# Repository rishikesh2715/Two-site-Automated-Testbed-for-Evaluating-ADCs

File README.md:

# Two-site-Automated-Testbed-for-Evaluating-ADCs

## Overview
The Two-site Automated Test System (ATS-2) is a custom-designed testbed for evaluating ADCs, specifically focused on testing the ADS7816. This comprehensive testing solution consists of a custom-designed device interface board, National Instruments VirtualBench integration, and automated test programs implemented in Python.

### Key Features:
- **Dual Testing Sites**: Capability to test two ADC devices simultaneously
- **Comprehensive Test Suite**: Includes all relevant parametric and functional tests
- **Automated Control**: Python-based test automation for consistent results
- **Relay-Based Interface**: Flexible configuration using G5NB-1A4 DC24 and J104D2C24VDC.15S relays
- **Power Management**: External 24V power supply for relay control

## Test Capabilities
The ATS-2 supports a comprehensive suite of tests including:
- Continuity Testing
- Power Supply Current Testing (Normal and Power-down modes)
- Leakage Current Testing
- Input Impedance Testing
- Linear Histogram Method for Code Edge Measurements
- Sinusoidal Histogram Method for Code Edge Measurements
- Offset and Offset Error Analysis
- Gain and Gain Error Analysis
- Missing Code Detection
- Integral Nonlinearity (INL) Analysis
- Differential Nonlinearity (DNL) Analysis
- Maximum Sampling Frequency Verification

## Hardware Specifications
### Device Under Test (DUT)
- **Target Device**: ADS7816
- **Features**: 
  - 200kHz sampling rate
  - Low power operation
  - Differential input
  - Serial interface
  - External reference and clock requirements
  - 5V power source operation

### Relay System
- **SPST-NO Relay**: G5NB-1A4 DC24
  - Power consumption: ~200mW
  - Operating current: ~8.3mA at 24V
  - Cost: $1.32

- **DPDT Relay**: J104D2C24VDC.15S
  - Power consumption: 150mW
  - Operating current: ~6.25mA at 24V
  - Cost: $1.21

## Software
The testbed includes a comprehensive suite of Python scripts for automated testing:
- `Combined_Hist_Tests.py`: Manages both linear and sinusoidal histogram testing
- `Continuity.py`: Performs continuity testing across all pins
- `InputImpedanceTest.py`: Measures input impedance characteristics
- `LeakageCurrents.py`: Tests for current leakage under various conditions
- `PwrSupplyCurrents.py`: Evaluates power supply current in different operating modes
- `Testing_Comb.py`: Main test orchestration script

## Getting Started
1. **Hardware Setup**:
   - Connect the VirtualBench device (VB8012-30DF182)
   - Apply 24V external power for relay control
   - Connect the DUT to the test board

2. **Software Requirements**:
   - Python 3.x
   - PyVirtualBench library
   - Required Python packages: numpy, matplotlib, tqdm, pandas

3. **Running Tests**:
   ```bash
   python Testing_Comb.py

## PCBWay - PCB Manufacturing and Assembly

This project was proudly sponsored by **PCBWay**, a leading PCB manufacturer and assembler. They provided high-quality PCB manufacturing and assembly services, ensuring that the ATS-2 board was produced to the highest standards. Here's why PCBWay is a great choice for PCB production:

- **Exceptional Quality**: The PCBs produced by PCBWay have excellent build quality, with precise soldering and thorough assembly.
- **Fast Service**: PCBWay offers quick turnaround times, so your project can stay on track.
- **Comprehensive Services**: From prototyping to mass production, PCBWay provides services for all stages of PCB development, including multi-layer PCBs, advanced PCBs, flexible PCBs, and assembly services.
- **Affordable Pricing**: PCBWay offers competitive pricing without compromising quality.

To order this board through PCBWay:
1. Upload the provided Gerber files to PCBWay's portal
2. Select your preferences:
   - Min Track/spacing: 6/6 mil
   - Min hole size: 0.2mm
   - Recommended finish: Immersion Gold (ENIG)

If you're looking for a reliable partner to bring your PCB projects to life, check out [PCBWay](https://pcbway.com). With their extensive capabilities and top-notch customer support, PCBWay is the ideal choice for makers, engineers, and businesses alike.

## PCB Features
- Custom designed device interface board
- Relay-based switching matrix for flexible test configuration
- Support for dual device testing
- Professional 4-layer PCB design
- Integrated power management for both DUT and relay control
- Comprehensive test point access
- Industrial-grade components for reliability

## License
This project is open-source and available under the MIT License.

## Contributing
Contributions are welcome! Please feel free to submit pull requests or open issues for improvements and bug fixes.

## Acknowledgments
- Mr. Johnston and Dr. Dallas at Texas Tech University for project supervision
- National Instruments for VirtualBench support
- PCBWay for manufacturing partnership

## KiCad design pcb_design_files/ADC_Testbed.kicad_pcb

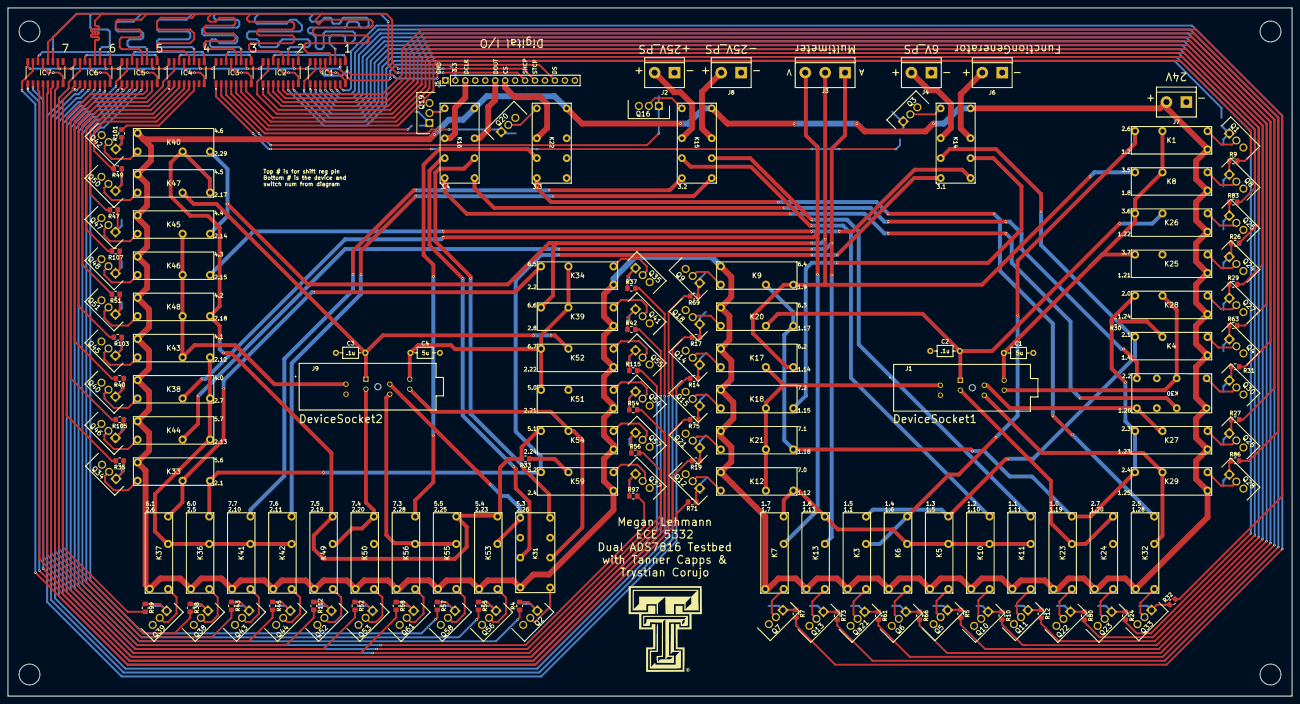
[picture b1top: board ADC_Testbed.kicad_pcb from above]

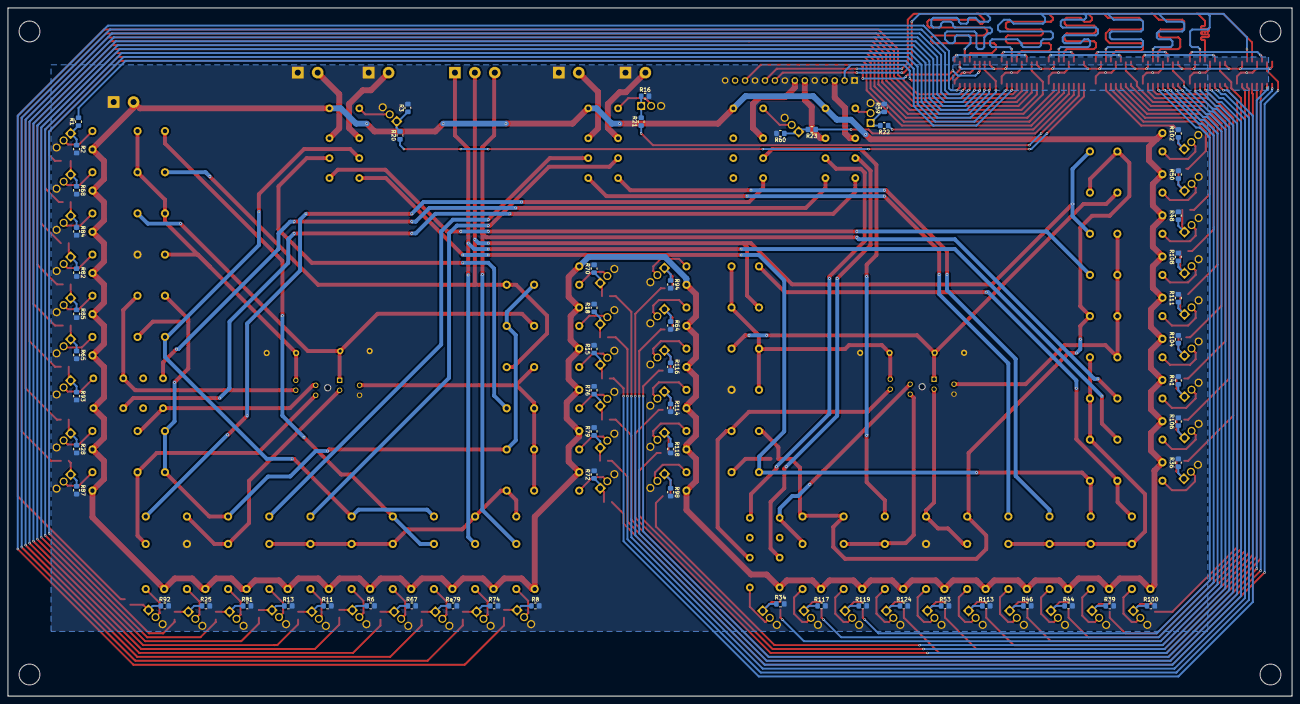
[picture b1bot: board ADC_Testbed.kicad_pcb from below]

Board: 2 copper layers, 327.5 x 175.5 mm, 238 parts (59 on the bottom side), 220 nets.

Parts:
C1, C4: 5u; C_Axial_L3.8mm_D2.6mm_P7.50mm_Horizontal
C2, C3: .1u; C_Axial_L3.8mm_D2.6mm_P7.50mm_Horizontal
IC1, IC2, IC3, IC4, IC5, IC6, IC7: 74LVC595AD_118; 74LVC595AD118
J1, J9: DNP; 3M_208-7391-55-1902
J2: +25V_PS; TerminalBlock_bornier-2_P5.08mm
J3: Multimeter; TerminalBlock_bornier-3_P5.08mm
J4: 6V_PS; TerminalBlock_bornier-2_P5.08mm
J5: Digital I/O; PinHeader_1x14_P2.54mm_Vertical
J6: FunctionGenerator; TerminalBlock_bornier-2_P5.08mm
J7: 24V; TerminalBlock_bornier-2_P5.08mm
J8: -25V_PS; TerminalBlock_bornier-2_P5.08mm
K1, K3, K4, K5, K6, K7, K8, K9, K10, K11, K12, K13, K17, K18, K20, K21, K23, K24, K25, K26, K27, K28, K29, K32, K33, K34, K36, K37, K38, K39, K40, K41, K42, K43, K44, K45, K46, K47, K48, K49, K50, K51, K52, K53, K54, K55, K56, K59: OJ-SS-112LMH2; G5NB1A4DC5
K14, K15, K16, K22, K30, K31: G6K-2P-Y_DC9; J104D2C24VDC.15S
Q1, Q2, Q3, Q4, Q5, Q6, Q7, Q8, Q9, Q10, Q11, Q12, Q13, Q14, Q15, Q16, Q18, Q19, Q20, Q21, Q22, Q23, Q24, Q25, Q26, Q27, Q28, Q30, Q33, Q34, Q35, Q37, Q38, Q39, Q40, Q41, Q42, Q43, Q44, Q45, Q46, Q47, Q48, Q50, Q51, Q52, Q53, Q54, Q55, Q56, Q57, Q58, Q61: IRL540PBF; TO254P465X1024X2050-3P
Qa21: IRL540PBF; TO254P465X1024X2050-3P
R1, R4, R5, R7, R9, R10, R12, R14, R17, R19, R20, R21, R22, R23, R24, R26, R27, R29, R31, R32, R35, R37, R38, R40, R42, R43, R45, R47, R49, R51, R52, R54, R55, R56, R57, R58, R61, R63, R66, R69, R71, R73, R75, R80, R83, R86, R97, R99, R101, R103, R105, R107, R112, R115: 2k; R_0805_2012Metric_Pad1.20x1.40mm_HandSolder
R2, R3, R6, R8, R11, R13, R15, R16, R18, R25, R28, R34, R36, R39, R41, R44, R46, R48, R50, R53, R59, R60, R64, R65, R67, R68, R70, R72, R74, R76, R79, R81, R82, R84, R85, R87, R92, R93, R94, R98, R100, R102, R104, R106, R108, R111, R113, R114, R116, R117, R118, R119, R124: 10k; R_0805_2012Metric_Pad1.20x1.40mm_HandSolder
R30, R33: 1R; R_0805_2012Metric_Pad1.20x1.40mm_HandSolder
Ra79: 10k; R_0805_2012Metric_Pad1.20x1.40mm_HandSolder

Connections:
0: J5.3, K16.6 (COM_2)
2: J5.6, K16.3 (COM_1)
3: J5.7, K22.6 (COM_2)
4: IC1.11 (SHCP), IC2.11 (SHCP), IC3.11 (SHCP), IC4.11 (SHCP), IC5.11 (SHCP), IC6.11 (SHCP), IC7.11 (SHCP), J5.9
5: IC1.12 (STCP), IC2.12 (STCP), IC3.12 (STCP), IC4.12 (STCP), IC5.12 (STCP), IC6.12 (STCP), IC7.12 (STCP), J5.10
6: IC1.14 (DS), J5.12
+3.3V: IC1.10 (~MR), IC1.16 (VCC), IC2.10 (~MR), IC2.16 (VCC), IC3.10 (~MR), IC3.16 (VCC), IC4.10 (~MR), IC4.16 (VCC), IC5.10 (~MR), IC5.16 (VCC), IC6.10 (~MR), IC6.16 (VCC), IC7.10 (~MR), IC7.16 (VCC), J5.2
+24V: J7.2, K1.2 (COIL_2), K3.2 (COIL_2), K4.2 (COIL_2), K5.2 (COIL_2), K6.2 (COIL_2), K7.2 (COIL_2), K8.2 (COIL_2), K9.2 (COIL_2), K10.2 (COIL_2), K11.2 (COIL_2), K12.2 (COIL_2), K13.2 (COIL_2), K14.1 (COIL_+), K15.1 (COIL_+), K16.1 (COIL_+), K17.2 (COIL_2), K18.2 (COIL_2), K20.2 (COIL_2), K21.2 (COIL_2), K22.1 (COIL_+), K23.2 (COIL_2), K24.2 (COIL_2), K25.2 (COIL_2), K26.2 (COIL_2), K27.2 (COIL_2), K28.2 (COIL_2), K29.2 (COIL_2), K30.1 (COIL_+), K31.1 (COIL_+), K32.2 (COIL_2), K33.2 (COIL_2), K34.2 (COIL_2), K36.2 (COIL_2), K37.2 (COIL_2), K38.2 (COIL_2), K39.2 (COIL_2), K40.2 (COIL_2), K41.2 (COIL_2), K42.2 (COIL_2), K43.2 (COIL_2), K44.2 (COIL_2), K45.2 (COIL_2), K46.2 (COIL_2), K47.2 (COIL_2), K48.2 (COIL_2), K49.2 (COIL_2), K50.2 (COIL_2), K51.2 (COIL_2), K52.2 (COIL_2), K53.2 (COIL_2), K54.2 (COIL_2), K55.2 (COIL_2), K56.2 (COIL_2), K59.2 (COIL_2)
+HighVoltage: J2.2, K15.6 (COM_2)
-HighVoltage: J8.2, K15.3 (COM_1)
/Relay_Control1/OUT: K1.3 (COM), K3.4 (NO), K6.3 (COM)
/Relay_Control2/OUT: C1.1, J1.8, K1.4 (NO), K8.4 (NO), K25.3 (COM), K26.3 (COM)
/Relay_Control4/OUT: K4.4 (NO), R30.1
/Relay_Control10/OUT: K5.4 (NO), K6.4 (NO), K7.3 (COM), K10.4 (NO), K11.4 (NO), K12.3 (COM), K13.3 (COM)
/Relay_Control12/OUT: J1.2, K12.4 (NO), K17.4 (NO), K18.4 (NO), K21.4 (NO)
/Relay_Control17/IN: K9.4 (NO), K20.3 (COM), K21.3 (COM), K23.3 (COM), K27.3 (COM), K28.3 (COM), K29.3 (COM), R30.2
/Relay_Control17/OUT: C2.2, J1.1, K20.4 (NO), K26.4 (NO)
/Relay_Control19/OUT: J1.3, K23.4 (NO), K24.3 (COM)
/Relay_Control23/OUT: J1.7, K27.4 (NO), K30.4 (N.O._1)
/Relay_Control24/OUT: J1.6, K28.4 (NO), K30.6 (COM_2)
/Relay_Control25/OUT: J1.5, K29.4 (NO), K32.4 (NO)
/Relay_Control29/OUT: K33.4 (NO), K34.3 (COM), K37.3 (COM)
/Relay_Control30/OUT: C4.1, J9.8, K34.4 (NO), K39.4 (NO), K51.3 (COM), K52.3 (COM)
/Relay_Control32/OUT: K59.4 (NO), R33.1
/Relay_Control33/OUT: K36.4 (NO), K37.4 (NO), K38.3 (COM), K41.4 (NO), K42.4 (NO), K43.3 (COM), K44.3 (COM)
/Relay_Control37/OUT: K40.4 (NO), K47.3 (COM), K48.3 (COM), K49.3 (COM), K53.3 (COM), K54.3 (COM), K55.3 (COM), R33.2
/Relay_Control40/OUT: J9.2, K43.4 (NO), K45.4 (NO), K46.4 (NO), K48.4 (NO)
/Relay_Control45/OUT: C3.2, J9.1, K47.4 (NO), K52.4 (NO)
/Relay_Control47/OUT: J9.3, K49.4 (NO), K50.3 (COM)
/Relay_Control51/OUT: J9.7, K31.4 (N.O._1), K53.4 (NO)
/Relay_Control52/OUT: J9.6, K31.6 (COM_2), K54.4 (NO)
/Relay_Control53/OUT: J9.5, K55.4 (NO), K56.4 (NO)
Ammeter: J3.1, K13.4 (NO), K44.4 (NO)
CS_1: IC3.1 (Q1), R20.1
CS_2: IC3.2 (Q2), R21.1
CS_3: IC3.4 (Q4), R22.1
CS_4: IC3.3 (Q3), R23.1
D1CS1: IC1.5 (Q5), R61.2
D1CS2: IC2.6 (Q6), R1.2
D1CS4: IC2.1 (Q1), R63.2
D1CS5: IC1.3 (Q3), R5.2
D1CS6: IC1.4 (Q4), R66.2
D1CS7: IC1.7 (Q7), R7.2
D1CS8: IC3.5 (Q5), R9.2
D1CS9: IC6.4 (Q4), R69.2
D1CS10: IC1.2 (Q2), R10.2
D1CS11: IC1.1 (Q1), R12.2
D1CS12: IC7.15 (Q0), R71.2
D1CS13: IC1.6 (Q6), R73.2
D1CS14: IC6.2 (Q2), R14.2
D1CS15: IC7.2 (Q2), R75.2
D1CS17: IC6.3 (Q3), R17.2
D1CS18: IC7.1 (Q1), R19.2
D1CS19: IC1.15 (Q0), R80.2
D1CS20: IC2.7 (Q7), R24.2
D1CS21: IC3.7 (Q7), R26.2
D1CS22: IC3.6 (Q6), R83.2
D1CS23: IC2.3 (Q3), R27.2
D1CS24: IC2.15 (Q0), R29.2
D1CS25: IC2.4 (Q4), R86.2
D1CS26: IC2.2 (Q2), R31.1
D1CS28: IC2.5 (Q5), R32.2
D1_+High: K10.3 (COM), K15.7 (N.C._2)
D1_-High: K11.3 (COM), K15.2 (N.C._1)
D1_CS: K22.5 (N.O._2), K32.3 (COM)
D1_DCLK: K16.5 (N.O._2), K30.3 (COM_1)
D1_DOUT: K16.4 (N.O._1), K30.5 (N.O._2)
D1_Low: K3.3 (COM), K4.3 (COM), K5.3 (COM), K14.7 (N.C._2)
D1_func: K14.2 (N.C._1), K18.3 (COM)
D2CS1: IC5.6 (Q6), R35.2
D2CS2: IC6.5 (Q5), R37.2
D2CS4: IC5.2 (Q2), R97.2
D2CS5: IC6.15 (Q0), R38.2
D2CS6: IC6.1 (Q1), R99.2
D2CS7: IC4.15 (Q0), R40.2
D2CS8: IC6.6 (Q6), R42.2
D2CS9: IC4.6 (Q6), R101.2
D2CS10: IC7.7 (Q7), R43.2
D2CS11: IC7.6 (Q6), R45.2
D2CS12: IC4.1 (Q1), R103.2
D2CS13: IC5.7 (Q7), R105.2
D2CS14: IC4.4 (Q4), R47.2
D2CS15: IC4.3 (Q3), R107.2
D2CS17: IC4.5 (Q5), R49.2
D2CS18: IC4.2 (Q2), R51.2
D2CS19: IC7.5 (Q5), R112.2
D2CS20: IC7.4 (Q4), R52.2
D2CS21: IC5.15 (Q0), R54.2
D2CS22: IC6.7 (Q7), R115.2
D2CS23: IC5.4 (Q4), R55.2
D2CS24: IC5.1 (Q1), R56.2
D2CS25: IC5.5 (Q5), R57.2
D2CS26: IC5.3 (Q3), R4.1
D2CS28: IC7.3 (Q3), R58.2
D2_+High: K15.5 (N.O._2), K41.3 (COM)
D2_-High: K15.4 (N.O._1), K42.3 (COM)
D2_CS: K22.7 (N.C._2), K56.3 (COM)
D2_DCLK: K16.7 (N.C._2), K31.3 (COM_1)
D2_DOUT: K16.2 (N.C._1), K31.5 (N.O._2)
D2_Low: K14.5 (N.O._2), K33.3 (COM), K36.3 (COM), K59.3 (COM)
D2_func: K14.4 (N.O._1), K46.3 (COM)
GND: C1.2, C2.1, C3.1, C4.2, IC1.8 (GND), IC1.13 (~OE), IC2.8 (GND), IC2.13 (~OE), IC3.8 (GND), IC3.13 (~OE), IC4.8 (GND), IC4.13 (~OE), IC5.8 (GND), IC5.13 (~OE), IC6.8 (GND), IC6.13 (~OE), IC7.8 (GND), IC7.13 (~OE), J1.4, J2.1, J4.1, J5.1, J5.5, J5.8, J5.11, J5.14, J6.1, J7.1, J8.1, J9.4, K24.4 (NO), K25.4 (NO), K50.4 (NO), K51.4 (NO), Q1.3 (S), Q2.3 (S), Q3.3 (S), Q4.3 (S), Q5.3 (S), Q6.3 (S), Q7.3 (S), Q8.3 (S), Q9.3 (S), Q10.3 (S), Q11.3 (S), Q12.3 (S), Q13.3 (S), Q14.3 (S), Q15.3 (S), Q16.3 (S), Q18.3 (S), Q19.3 (S), Q20.3 (S), Q21.3 (S), Q22.3 (S), Q23.3 (S), Q24.3 (S), Q25.3 (S), Q26.3 (S), Q27.3 (S), Q28.3 (S), Q30.3 (S), Q33.3 (S), Q34.3 (S), Q35.3 (S), Q37.3 (S), Q38.3 (S), Q39.3 (S), Q40.3 (S), Q41.3 (S), Q42.3 (S), Q43.3 (S), Q44.3 (S), Q45.3 (S), Q46.3 (S), Q47.3 (S), Q48.3 (S), Q50.3 (S), Q51.3 (S), Q52.3 (S), Q53.3 (S), Q54.3 (S), Q55.3 (S), Q56.3 (S), Q57.3 (S), Q58.3 (S), Q61.3 (S), Qa21.3 (S), R2.2, R3.2, R6.2, R8.2, R11.2, R13.2, R15.2, R16.2, R18.2, R25.2, R28.2, R34.2, R36.2, R39.2, R41.2, R44.2, R46.2, R48.2, R50.2, R53.2, R59.2, R60.2, R64.2, R65.2, R67.2, R68.2, R70.2, R72.2, R74.2, R76.2, R79.2, R81.2, R82.2, R84.2, R85.2, R87.2, R92.2, R93.2, R94.2, R98.2, R100.2, R102.2, R104.2, R106.2, R108.2, R111.2, R113.2, R114.2, R116.2, R117.2, R118.2, R119.2, R124.2, Ra79.2
LowVoltage: J4.2, K14.6 (COM_2)
MultiOut: J3.2, K8.3 (COM), K9.3 (COM), K17.3 (COM), K39.3 (COM), K40.3 (COM), K45.3 (COM)
unnamed: IC1.9 (Q7S), IC2.14 (DS)
unnamed: IC2.9 (Q7S), IC3.14 (DS)
unnamed: IC3.9 (Q7S), IC4.14 (DS)
unnamed: IC4.9 (Q7S), IC5.14 (DS)
unnamed: IC5.9 (Q7S), IC6.14 (DS)
unnamed: IC6.9 (Q7S), IC7.14 (DS)
unnamed: K1.1 (COIL_1), Q1.2 (D)
unnamed: K3.1 (COIL_1), Qa21.2 (D)
unnamed: K4.1 (COIL_1), Q4.2 (D)
unnamed: K5.1 (COIL_1), Q5.2 (D)
unnamed: K6.1 (COIL_1), Q6.2 (D)
unnamed: K7.1 (COIL_1), Q7.2 (D)
unnamed: K8.1 (COIL_1), Q8.2 (D)
unnamed: K9.1 (COIL_1), Q9.2 (D)
unnamed: K10.1 (COIL_1), Q10.2 (D)
unnamed: K11.1 (COIL_1), Q11.2 (D)
unnamed: K12.1 (COIL_1), Q12.2 (D)
unnamed: K13.1 (COIL_1), Q13.2 (D)
unnamed: K14.8 (COIL_-), Q3.2 (D)
unnamed: K15.8 (COIL_-), Q16.2 (D)
unnamed: K16.8 (COIL_-), Q19.2 (D)
unnamed: K17.1 (COIL_1), Q14.2 (D)
unnamed: K18.1 (COIL_1), Q15.2 (D)
unnamed: K20.1 (COIL_1), Q18.2 (D)
unnamed: K21.1 (COIL_1), Q21.2 (D)
unnamed: K22.8 (COIL_-), Q20.2 (D)
unnamed: K23.1 (COIL_1), Q22.2 (D)
unnamed: K24.1 (COIL_1), Q23.2 (D)
unnamed: K25.1 (COIL_1), Q24.2 (D)
unnamed: K26.1 (COIL_1), Q25.2 (D)
unnamed: K27.1 (COIL_1), Q26.2 (D)
unnamed: K28.1 (COIL_1), Q27.2 (D)
unnamed: K29.1 (COIL_1), Q28.2 (D)
unnamed: K30.8 (COIL_-), Q30.2 (D)
unnamed: K31.8 (COIL_-), Q2.2 (D)
unnamed: K32.1 (COIL_1), Q33.2 (D)
unnamed: K33.1 (COIL_1), Q34.2 (D)
unnamed: K34.1 (COIL_1), Q35.2 (D)
unnamed: K36.1 (COIL_1), Q38.2 (D)
unnamed: K37.1 (COIL_1), Q39.2 (D)
unnamed: K38.1 (COIL_1), Q40.2 (D)
unnamed: K39.1 (COIL_1), Q41.2 (D)
unnamed: K40.1 (COIL_1), Q42.2 (D)
unnamed: K41.1 (COIL_1), Q43.2 (D)
unnamed: K42.1 (COIL_1), Q44.2 (D)
unnamed: K43.1 (COIL_1), Q45.2 (D)
unnamed: K44.1 (COIL_1), Q46.2 (D)
unnamed: K45.1 (COIL_1), Q47.2 (D)
unnamed: K46.1 (COIL_1), Q48.2 (D)
unnamed: K47.1 (COIL_1), Q50.2 (D)
unnamed: K48.1 (COIL_1), Q51.2 (D)
unnamed: K49.1 (COIL_1), Q52.2 (D)
unnamed: K50.1 (COIL_1), Q53.2 (D)
unnamed: K51.1 (COIL_1), Q54.2 (D)
unnamed: K52.1 (COIL_1), Q55.2 (D)
unnamed: K53.1 (COIL_1), Q56.2 (D)
unnamed: K54.1 (COIL_1), Q57.2 (D)
unnamed: K55.1 (COIL_1), Q58.2 (D)
unnamed: K56.1 (COIL_1), Q61.2 (D)
unnamed: K59.1 (COIL_1), Q37.2 (D)
unnamed: Q1.1 (G), R1.1, R2.1
unnamed: Q2.1 (G), R4.2, R34.1
unnamed: Q3.1 (G), R3.1, R20.2
unnamed: Q4.1 (G), R63.1, R65.1
unnamed: Q5.1 (G), R5.1, R6.1
unnamed: Q6.1 (G), R66.1, R67.1
unnamed: Q7.1 (G), R7.1, R8.1
unnamed: Q8.1 (G), R9.1, R68.1
unnamed: Q9.1 (G), R69.1, R70.1
unnamed: Q10.1 (G), R10.1, R11.1
unnamed: Q11.1 (G), R12.1, R13.1
unnamed: Q12.1 (G), R71.1, R72.1
unnamed: Q13.1 (G), R73.1, R74.1
unnamed: Q14.1 (G), R14.1, R15.1
unnamed: Q15.1 (G), R75.1, R76.1
unnamed: Q16.1 (G), R16.1, R21.2
unnamed: Q18.1 (G), R17.1, R18.1
unnamed: Q19.1 (G), R22.2, R59.1
unnamed: Q20.1 (G), R23.2, R60.1
unnamed: Q21.1 (G), R19.1, R79.1
unnamed: Q22.1 (G), R80.1, R81.1
unnamed: Q23.1 (G), R24.1, R25.1
unnamed: Q24.1 (G), R26.1, R82.1
unnamed: Q25.1 (G), R83.1, R84.1
unnamed: Q26.1 (G), R27.1, R28.1
unnamed: Q27.1 (G), R29.1, R85.1
unnamed: Q28.1 (G), R86.1, R87.1
unnamed: Q30.1 (G), R31.2, R93.1
unnamed: Q33.1 (G), R32.1, R92.1
unnamed: Q34.1 (G), R35.1, R36.1
unnamed: Q35.1 (G), R37.1, R94.1
unnamed: Q37.1 (G), R97.1, R98.1
unnamed: Q38.1 (G), R38.1, R39.1
unnamed: Q39.1 (G), R99.1, R100.1
unnamed: Q40.1 (G), R40.1, R41.1
unnamed: Q41.1 (G), R42.1, R64.1
unnamed: Q42.1 (G), R101.1, R102.1
unnamed: Q43.1 (G), R43.1, R44.1
unnamed: Q44.1 (G), R45.1, R46.1
unnamed: Q45.1 (G), R103.1, R104.1
unnamed: Q46.1 (G), R105.1, R106.1
unnamed: Q47.1 (G), R47.1, R48.1
unnamed: Q48.1 (G), R107.1, R108.1
unnamed: Q50.1 (G), R49.1, R50.1
unnamed: Q51.1 (G), R51.1, R111.1
unnamed: Q52.1 (G), R112.1, R113.1
unnamed: Q53.1 (G), R52.1, R53.1
unnamed: Q54.1 (G), R54.1, R114.1
unnamed: Q55.1 (G), R115.1, R116.1
unnamed: Q56.1 (G), R55.1, R117.1
unnamed: Q57.1 (G), R56.1, R118.1
unnamed: Q58.1 (G), R57.1, R119.1
unnamed: Q61.1 (G), R58.1, R124.1
unnamed: Qa21.1 (G), R61.1, Ra79.1
Voltmeter: J3.3, K7.4 (NO), K38.4 (NO)
function: J6.2, K14.3 (COM_1)

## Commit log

2025-01-04 added pcbway logo
2025-01-04 added python files
2025-01-04 added kicad design files
2025-01-04 added BOM for the PCB
